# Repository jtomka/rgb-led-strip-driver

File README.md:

# 12V RGB LED Strip Driver

12V driven by power MOSFETs, controlled by three 3V3-5V GPIOs.

To be powered by a 12VDC/5A power supply, enough to drive 300 diodes,
typically 5M in length. Includes a 5V voltage regulator for the MCU
board.

At 75MM x 25MM, the board comes with enough space for a vertically
placed Waveshare ESP32-S3-Zero, but can be controlled via three GPIOs
from any source.

#### Sources of Information:

* https://learn.adafruit.com/rgb-led-strips/usage
* https://kno.wled.ge/basics/compatible-led-strips/#non-addressable-led-strips

#### Using With Waveshare ESP-S3-Zero and WLED

* https://github.com/jtomka/wled-esp32-s3-zero

#### Images

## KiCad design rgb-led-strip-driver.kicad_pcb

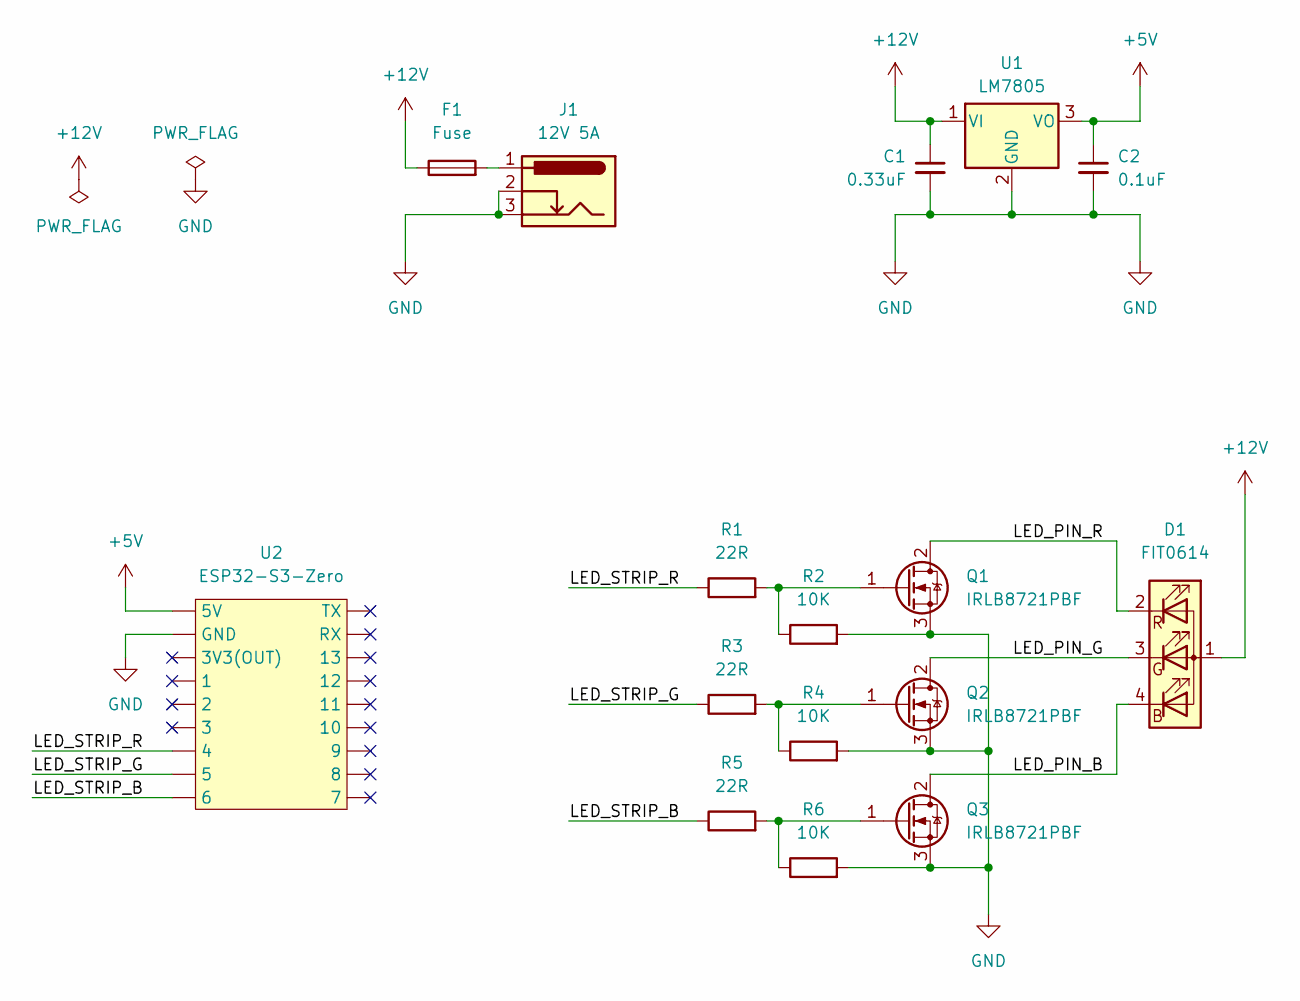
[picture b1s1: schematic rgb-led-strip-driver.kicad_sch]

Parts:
C1: 0.33uF; C_Disc_D7.5mm_W2.5mm_P5.00mm
C2: 0.1uF; C_Disc_D7.5mm_W2.5mm_P5.00mm
D1: FIT0614; PinHeader_1x04_P2.54mm_Vertical
F1: Fuse; FuseHolder_Blade_ATO_Littelfuse_FLR_178.6165
J1: 12V 5A; BarrelJack_Horizontal
Q1, Q2, Q3: IRLB8721PBF; TO-220-3_Vertical
R1, R3, R5: 22R; R_Axial_DIN0204_L3.6mm_D1.6mm_P5.08mm_Horizontal
R2, R4, R6: 10K; R_Axial_DIN0204_L3.6mm_D1.6mm_P5.08mm_Horizontal
U1: LM7805; TO-220-3_Vertical
U2: ESP32-S3-Zero; PinHeader_1x09_P2.54mm_Vertical

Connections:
+5V: C2.1, U1.3 (VO), U2.1 (5V)
+12V: C1.1, D1.1 (A), F1.1, U1.1 (VI)
/LED_PIN_B: D1.4 (BK), Q3.2 (D)
/LED_PIN_G: D1.3 (GK), Q2.2 (D)
/LED_PIN_R: D1.2 (RK), Q1.2 (D)
/LED_STRIP_B: R5.1, U2.9 (6)
/LED_STRIP_G: R3.1, U2.8 (5)
/LED_STRIP_R: R1.1, U2.7 (4)
GND: C1.2, C2.2, J1.2, J1.3, Q1.3 (S), Q2.3 (S), Q3.3 (S), R2.2, R4.2, R6.2, U1.2 (GND), U2.2 (GND)
unnamed: F1.2, J1.1
unnamed: Q1.1 (G), R1.2, R2.1
unnamed: Q2.1 (G), R3.2, R4.1
unnamed: Q3.1 (G), R5.2, R6.1

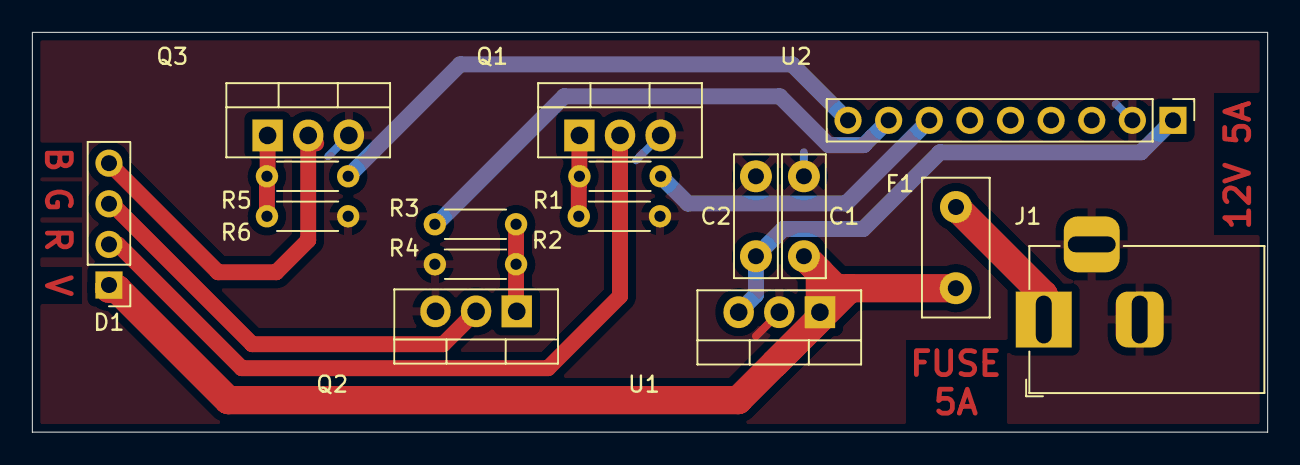
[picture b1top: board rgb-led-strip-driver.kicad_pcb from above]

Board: 2 copper layers, 77.2 x 25.0 mm, 16 parts (0 on the bottom side), 13 nets.

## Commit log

2024-12-29 Update README, add image
